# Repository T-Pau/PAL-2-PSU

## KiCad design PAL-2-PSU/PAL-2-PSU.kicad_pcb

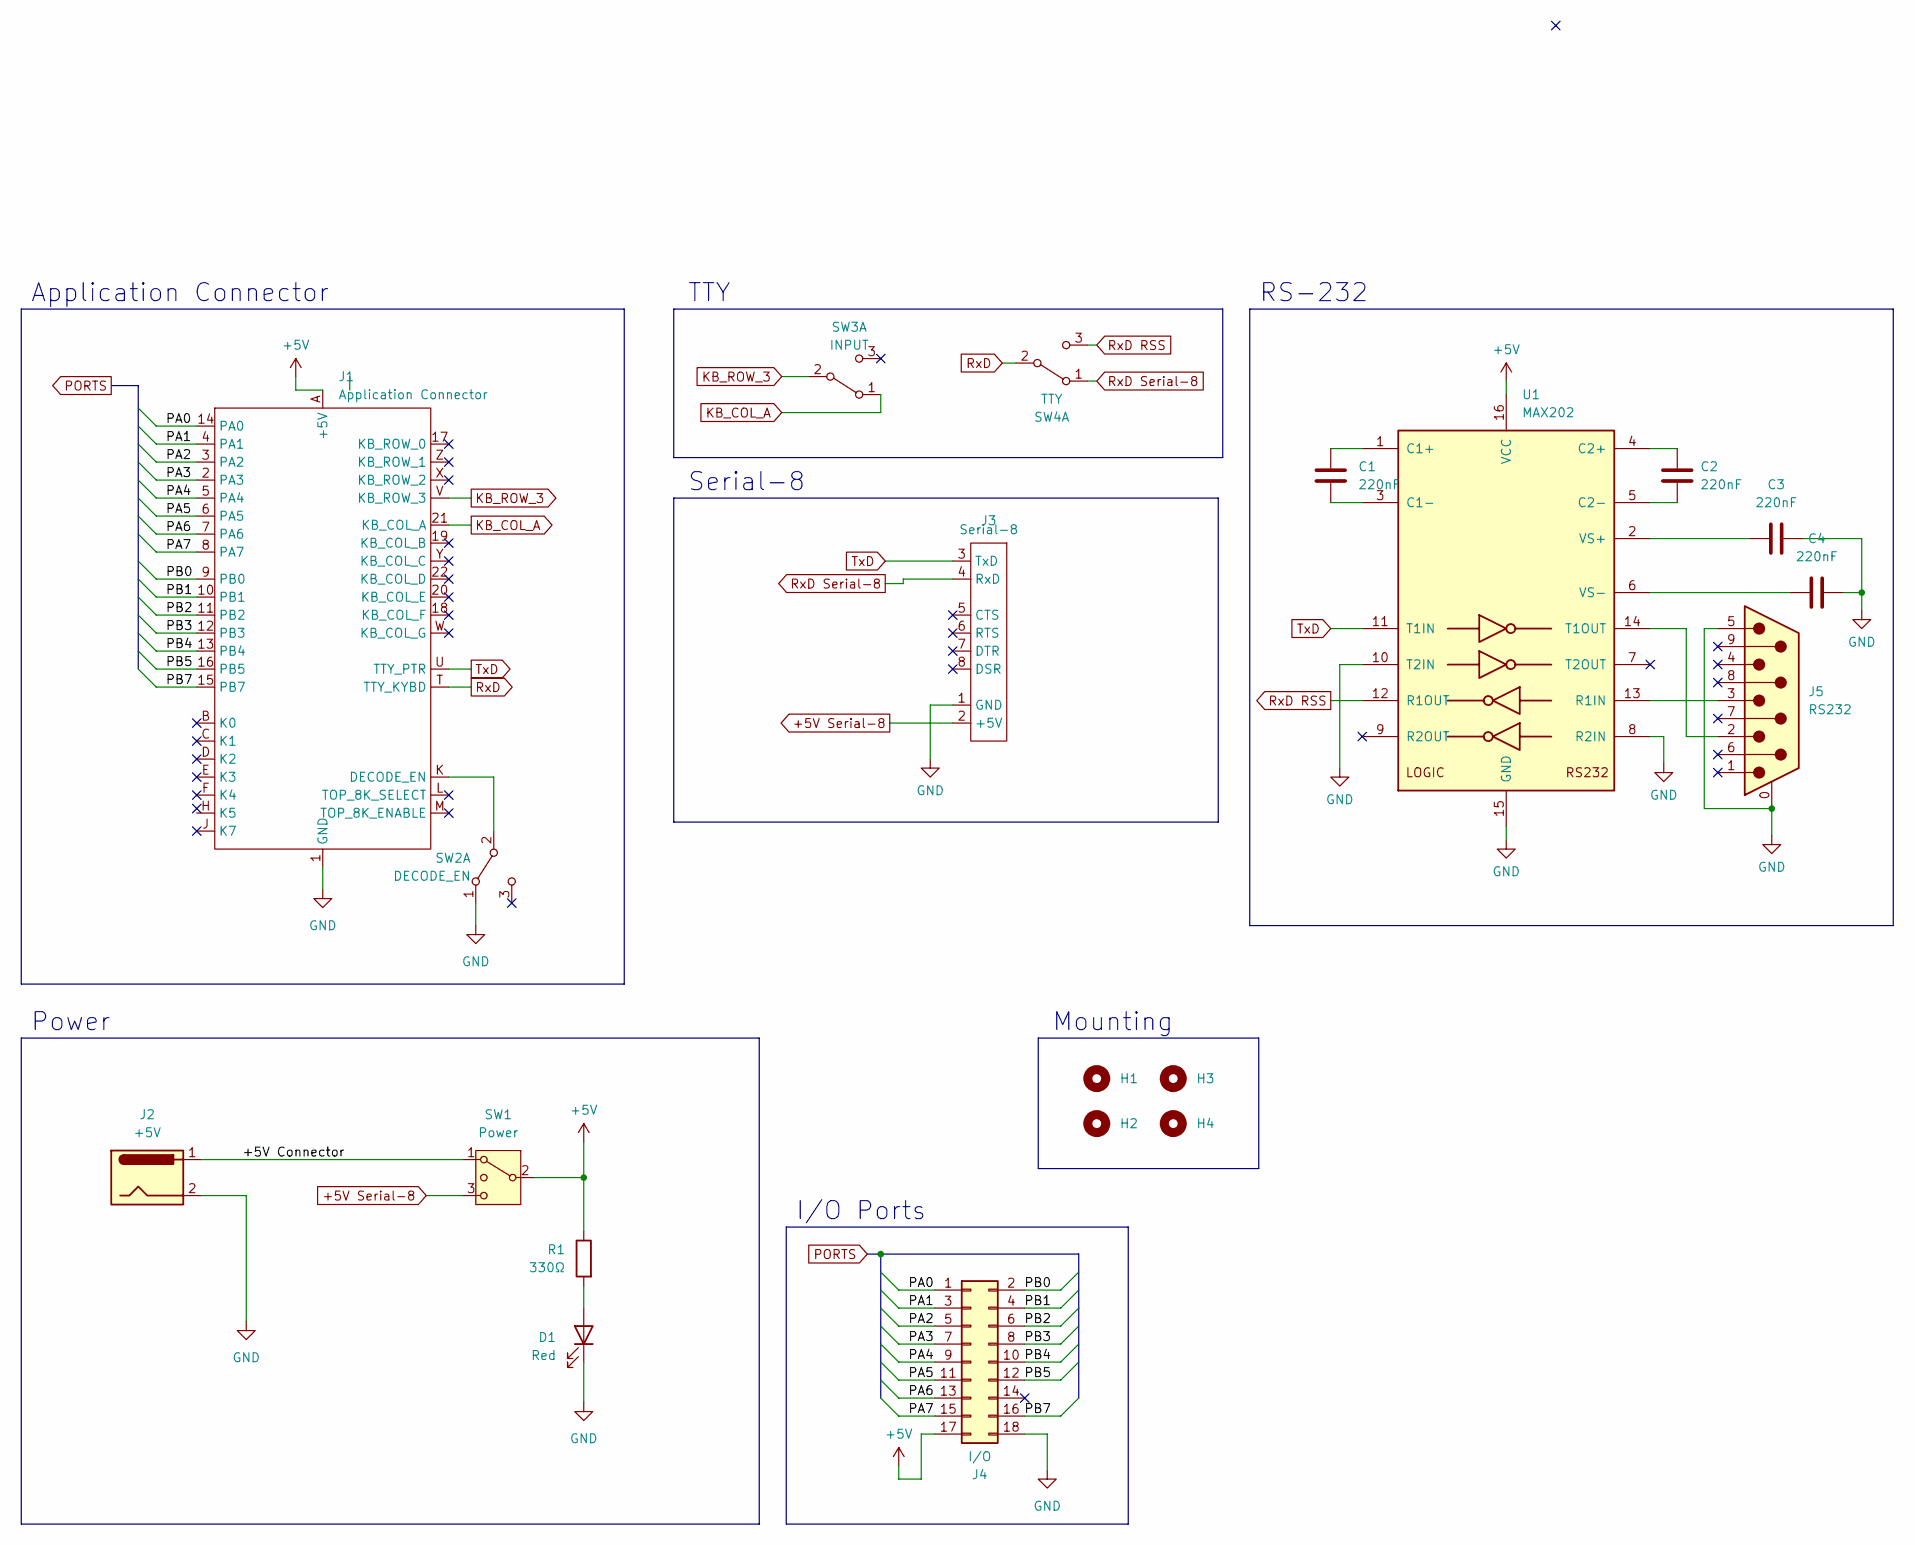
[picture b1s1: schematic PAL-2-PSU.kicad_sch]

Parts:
C1, C2, C3, C4: 220nF; C_Disc_D5.0mm_W2.5mm_P5.00mm
D1: Red; LED_D5.0mm
H1, H2, H3, H4: MountingHole_3.2mm_M3
J1: Application Connector; PAL-2 Connector
J2: +5V; BarrelJack_Horizontal
J3: Serial-8; IDC-Header_2x04_P2.54mm_Vertical
J4: I/O; PinHeader_2x09_P2.54mm_Vertical
J5: RS232; DSUB-9_Male_Horizontal_P2.77x2.84mm_EdgePinOffset4.94mm_Hou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
R1: 330Ω; R_Axial_DIN0309_L9.0mm_D3.2mm_P12.70mm_Horizontal
SW1: Power; SS2513
SW2: DECODE_EN; SS2513
SW3: INPUT; SS2513
SW4: TTY; SS2513
U1: MAX202; DIP-16_W7.62mm_Socket_LongPads

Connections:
+5V: J1.A (+5V), J4.17, R1.1, SW1.2 (3), U1.16 (VCC)
+5V Serial-8: J3.2 (+5V), SW1.3 (4)
/+5V Connector: J2.1, SW1.1
/PA0: J1.14 (PA0), J4.1
/PA1: J1.4 (PA1), J4.3
/PA2: J1.3 (PA2), J4.5
/PA3: J1.2 (PA3), J4.7
/PA4: J1.5 (PA4), J4.9
/PA5: J1.6 (PA5), J4.11
/PA6: J1.7 (PA6), J4.13
/PA7: J1.8 (PA7), J4.15
/PB0: J1.9 (PB0), J4.2
/PB1: J1.10 (PB1), J4.4
/PB2: J1.11 (PB2), J4.6
/PB3: J1.12 (PB3), J4.8
/PB4: J1.13 (PB4), J4.10
/PB5: J1.16 (PB5), J4.12
/PB7: J1.15 (PB7), J4.16
GND: C3.1, C4.1, D1.1 (K), J1.1 (GND), J2.2, J3.1 (GND), J4.18, J5.0 (PAD), J5.5, SW2.1 (A), U1.8 (R2IN), U1.10 (T2IN), U1.15 (GND)
KB_COL_A: J1.21 (KB_COL_A), SW3.1 (A)
KB_ROW_3: J1.V (KB_ROW_3), SW3.2 (B)
unnamed: D1.2 (A), R1.2
unnamed: J1.K (DECODE_EN), SW2.2 (B)
unnamed: C1.1, U1.1 (C1+)
unnamed: C1.2, U1.3 (C1-)
unnamed: C2.1, U1.4 (C2+)
unnamed: C2.2, U1.5 (C2-)
unnamed: J5.3, U1.13 (R1IN)
unnamed: J5.2, U1.14 (T1OUT)
unnamed: C3.2, U1.2 (VS+)
unnamed: C4.2, U1.6 (VS-)
RxD: J1.T (TTY_KYBD), SW4.2 (B)
RxD RSS: SW4.3 (C), U1.12 (R1OUT)
RxD Serial-8: J3.4 (RxD), SW4.1 (A)
TxD: J1.U (TTY_PTR), J3.3 (TxD), U1.11 (T1IN)

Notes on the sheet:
Mounting
TTY
Power
Application Connector
Serial-8
RS-232
I/O Ports

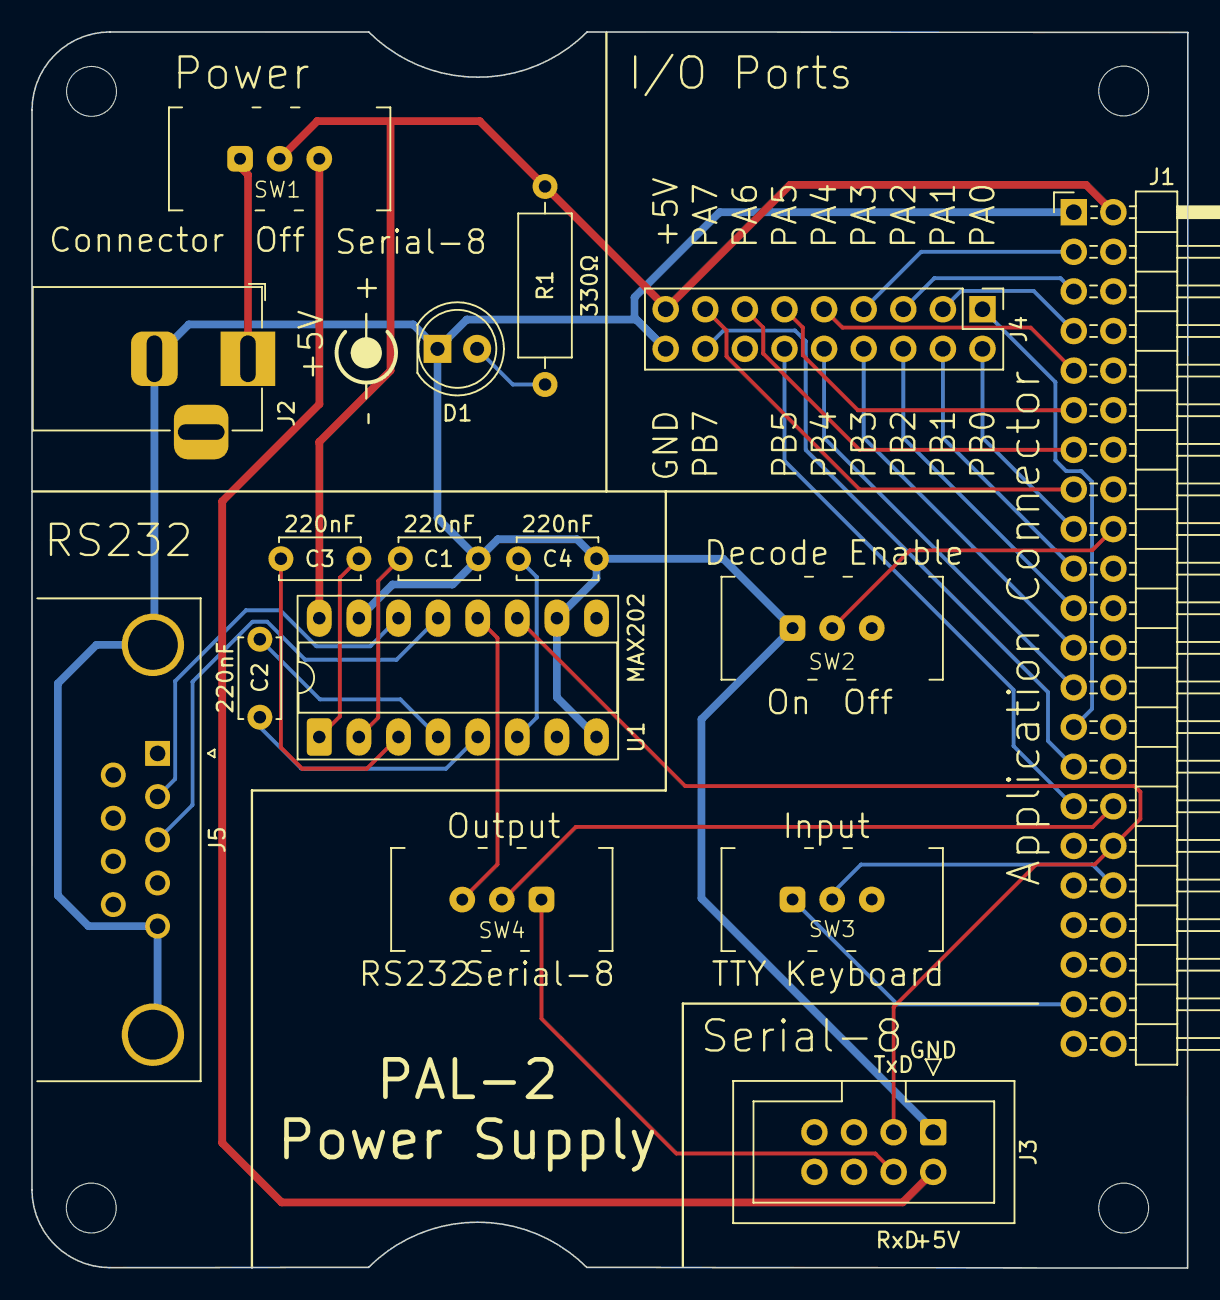
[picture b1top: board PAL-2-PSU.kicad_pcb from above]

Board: 2 copper layers, 74.1 x 79.3 mm, 20 parts (0 on the bottom side), 35 nets.

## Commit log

2025-04-26 FInish PCB.
2025-04-27 Use 2.54/5.08mm footprint for power switch.
    Label Serial-8 pins.
2025-06-23 Fix missing trace, make switch positions more logical.

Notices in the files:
PAL-2-PSU/PAL-2-PSU.kicad_pcb:
©2025 Dieter Baron
